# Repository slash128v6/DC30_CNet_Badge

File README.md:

DEF CON 30 CompuNet Badge

Check out the Docs folder...

Here is an informational 'BadUSB'course from the creator of the WiFi Duck: https://learnbadusb.com/ (we are not affiliated and we don't make any money on this)

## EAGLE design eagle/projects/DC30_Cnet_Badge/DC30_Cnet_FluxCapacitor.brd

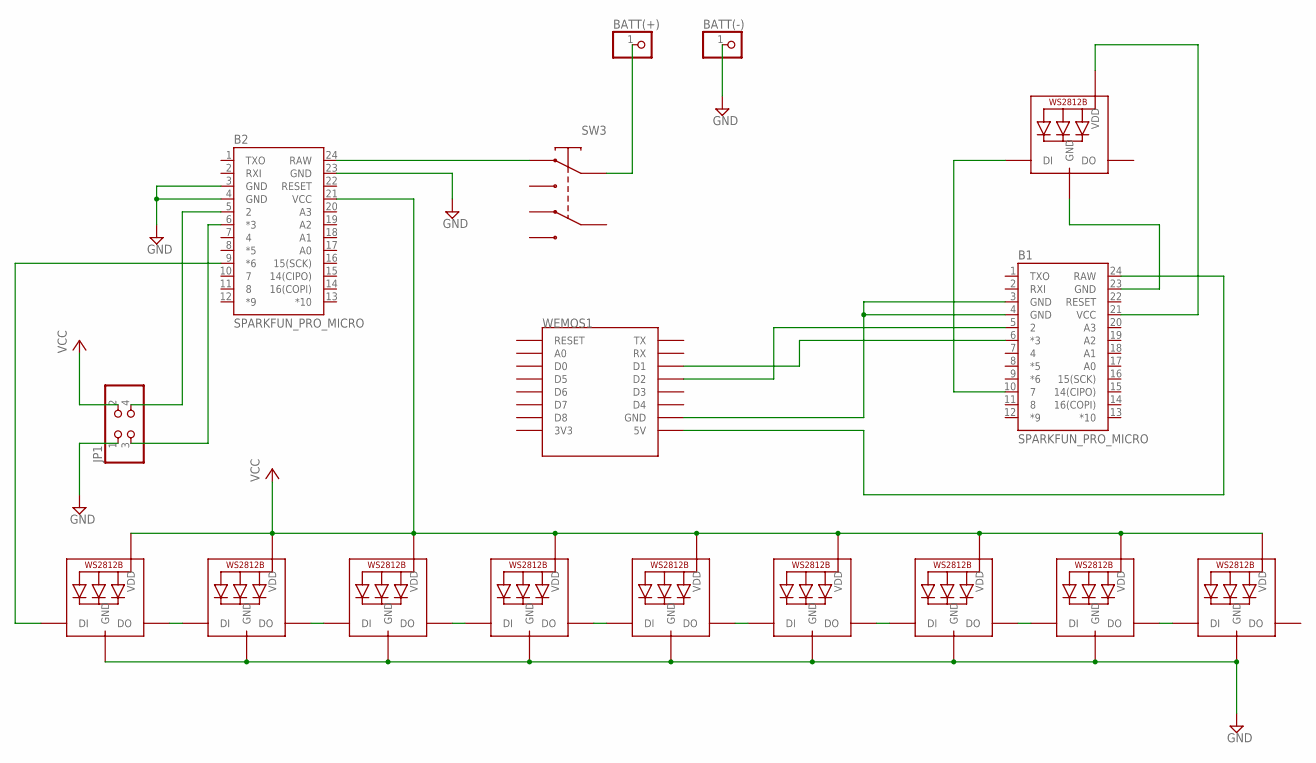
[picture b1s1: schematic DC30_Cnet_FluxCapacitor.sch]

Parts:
B1, B2: SPARKFUN_PRO_MICRO
BATT(+): PINHD-1X1; 1X01
BATT(-): PINHD-1X1; 1X01
JP1: PINHD-2X2; 2X02
LED1, LED2, LED3, LED4, LED5, LED6, LED7, LED8, LED9, LED10: WS2812B5050; WS2812B
SW3: JS202011AQN
WEMOS1: WEMOS-D1-MINI

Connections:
GND: B2.3 (GND), B2.4 (GND), B2.23 (GND), BATT(-).1, JP1.1, LED1.3-GND (GND), LED2.3-GND (GND), LED3.3-GND (GND), LED4.3-GND (GND), LED5.3-GND (GND), LED6.3-GND (GND), LED7.3-GND (GND), LED8.3-GND (GND), LED9.3-GND (GND)
unnamed: B1.10 (7), LED10.4-DIN (DI)
unnamed: BATT(+).1, SW3.P$2 (2)
unnamed: B2.9 (*6), LED1.4-DIN (DI)
unnamed: LED1.2-DOUT (DO), LED2.4-DIN (DI)
unnamed: LED2.2-DOUT (DO), LED3.4-DIN (DI)
unnamed: LED3.2-DOUT (DO), LED4.4-DIN (DI)
unnamed: LED4.2-DOUT (DO), LED5.4-DIN (DI)
unnamed: LED5.2-DOUT (DO), LED6.4-DIN (DI)
unnamed: LED6.2-DOUT (DO), LED7.4-DIN (DI)
unnamed: LED7.2-DOUT (DO), LED8.4-DIN (DI)
unnamed: LED8.2-DOUT (DO), LED9.4-DIN (DI)
unnamed: B2.5 (2), JP1.4
unnamed: B1.3 (GND), B1.4 (GND), WEMOS1.GND
unnamed: B1.24 (RAW), WEMOS1.5V
unnamed: B1.23 (GND), LED10.3-GND (GND)
unnamed: B1.21 (VCC), LED10.1-VDD (VDD)
unnamed: B1.5 (2), WEMOS1.D2
unnamed: B1.6 (*3), WEMOS1.D1
unnamed: B2.6 (*3), JP1.3
unnamed: B2.24 (RAW), SW3.P$1 (1)
VCC: B2.21 (VCC), JP1.2, LED1.1-VDD (VDD), LED2.1-VDD (VDD), LED3.1-VDD (VDD), LED4.1-VDD (VDD), LED5.1-VDD (VDD), LED6.1-VDD (VDD), LED7.1-VDD (VDD), LED8.1-VDD (VDD), LED9.1-VDD (VDD)

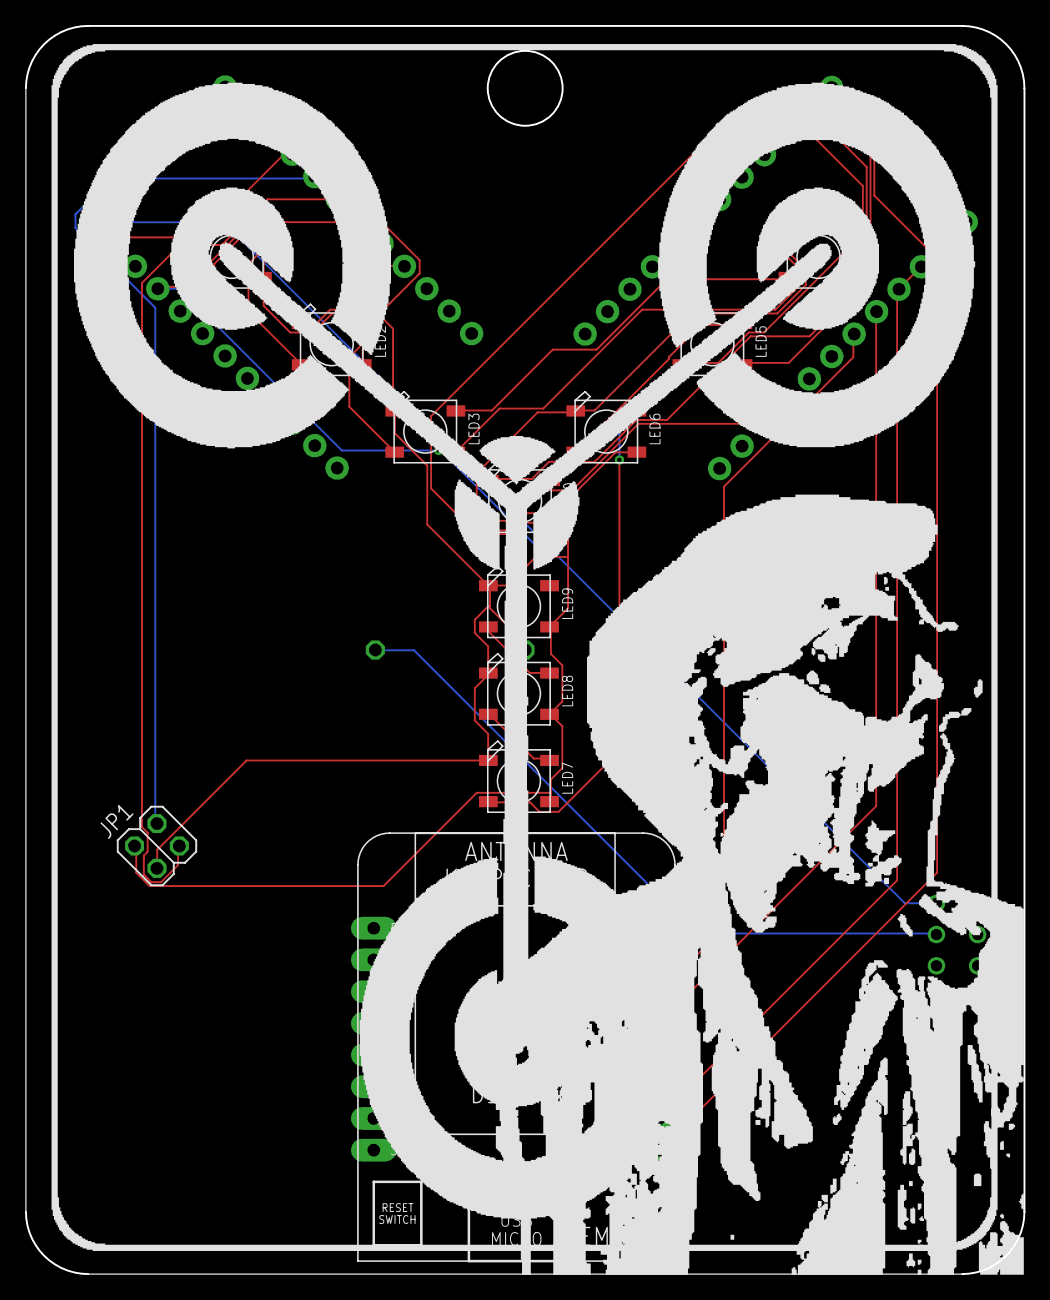
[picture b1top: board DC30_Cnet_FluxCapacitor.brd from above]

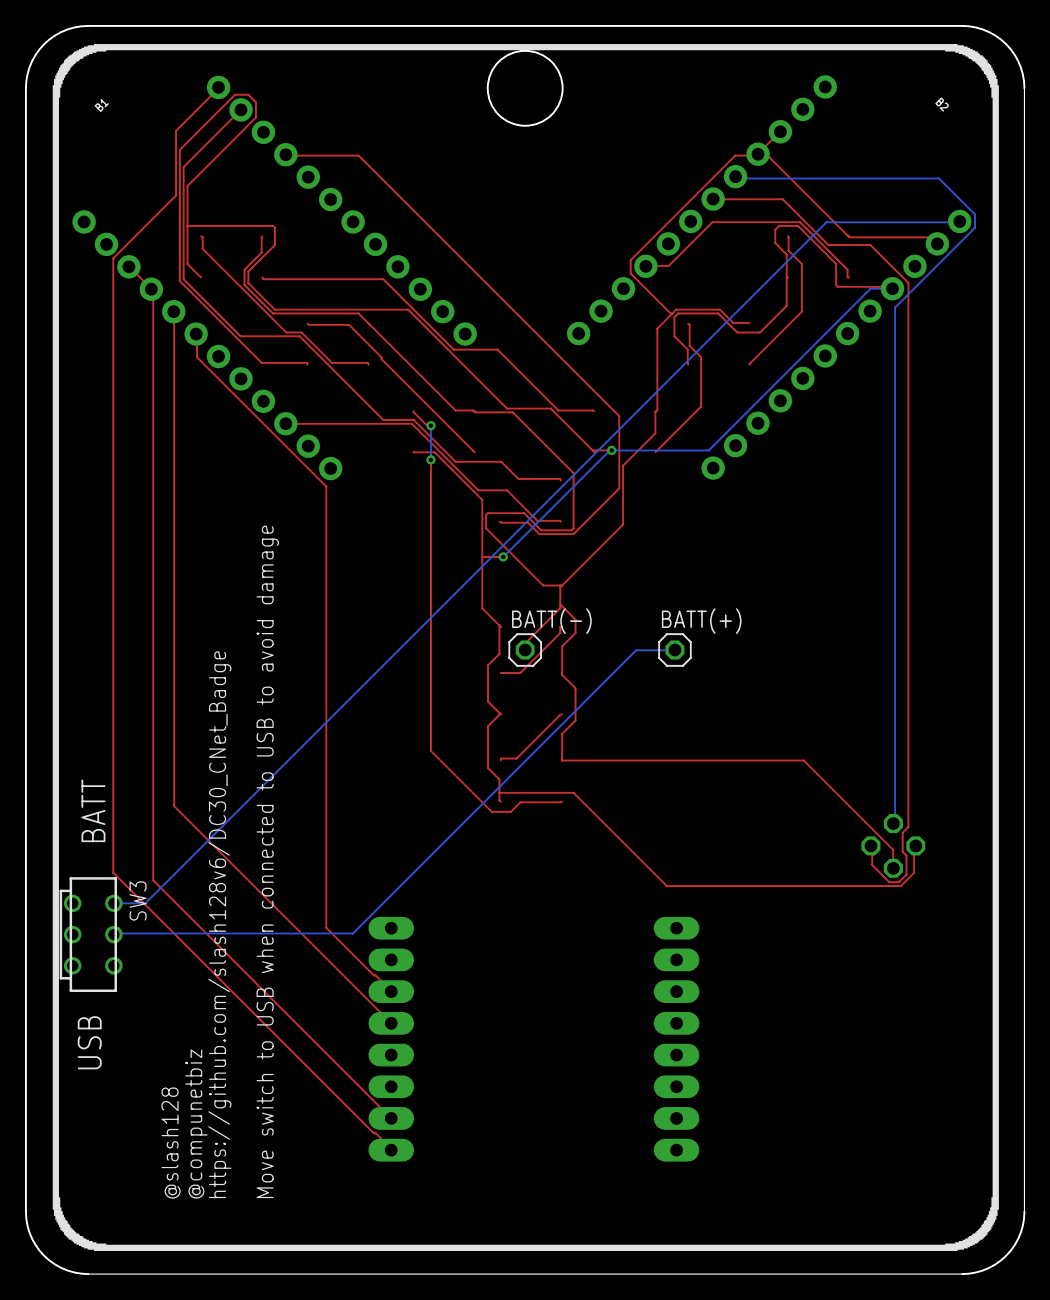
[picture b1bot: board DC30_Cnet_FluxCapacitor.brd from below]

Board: 2 copper layers, 80.0 x 100.0 mm, 17 parts (5 on the bottom side), 22 nets.

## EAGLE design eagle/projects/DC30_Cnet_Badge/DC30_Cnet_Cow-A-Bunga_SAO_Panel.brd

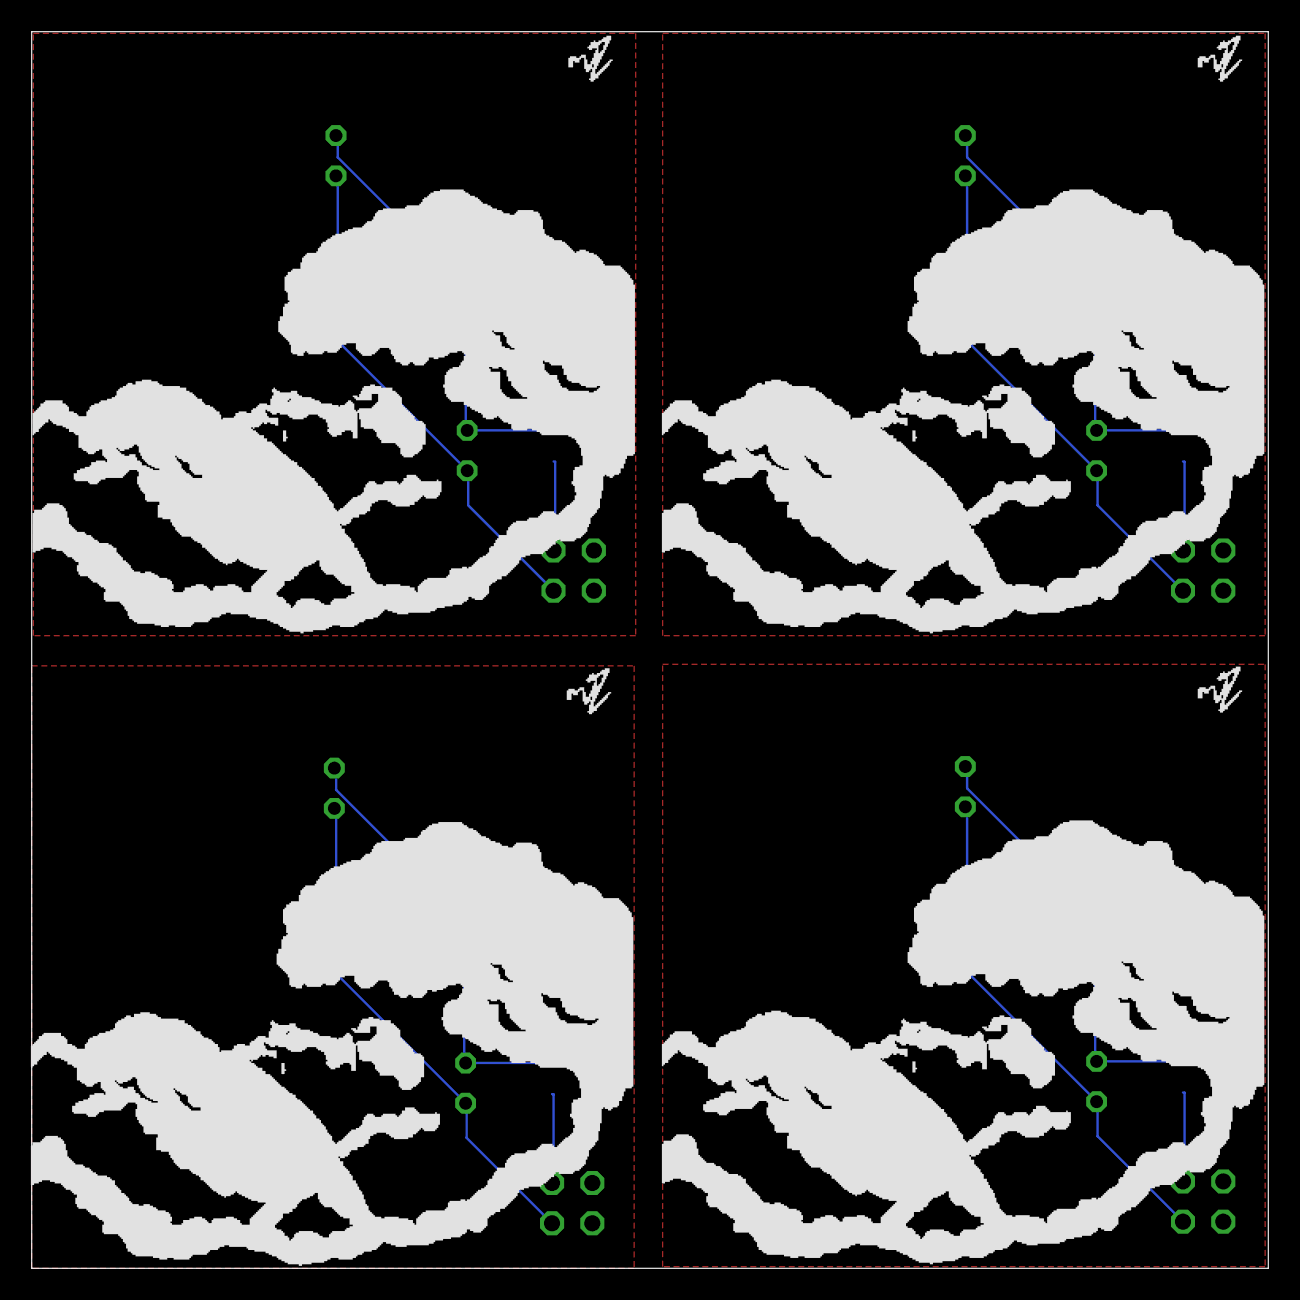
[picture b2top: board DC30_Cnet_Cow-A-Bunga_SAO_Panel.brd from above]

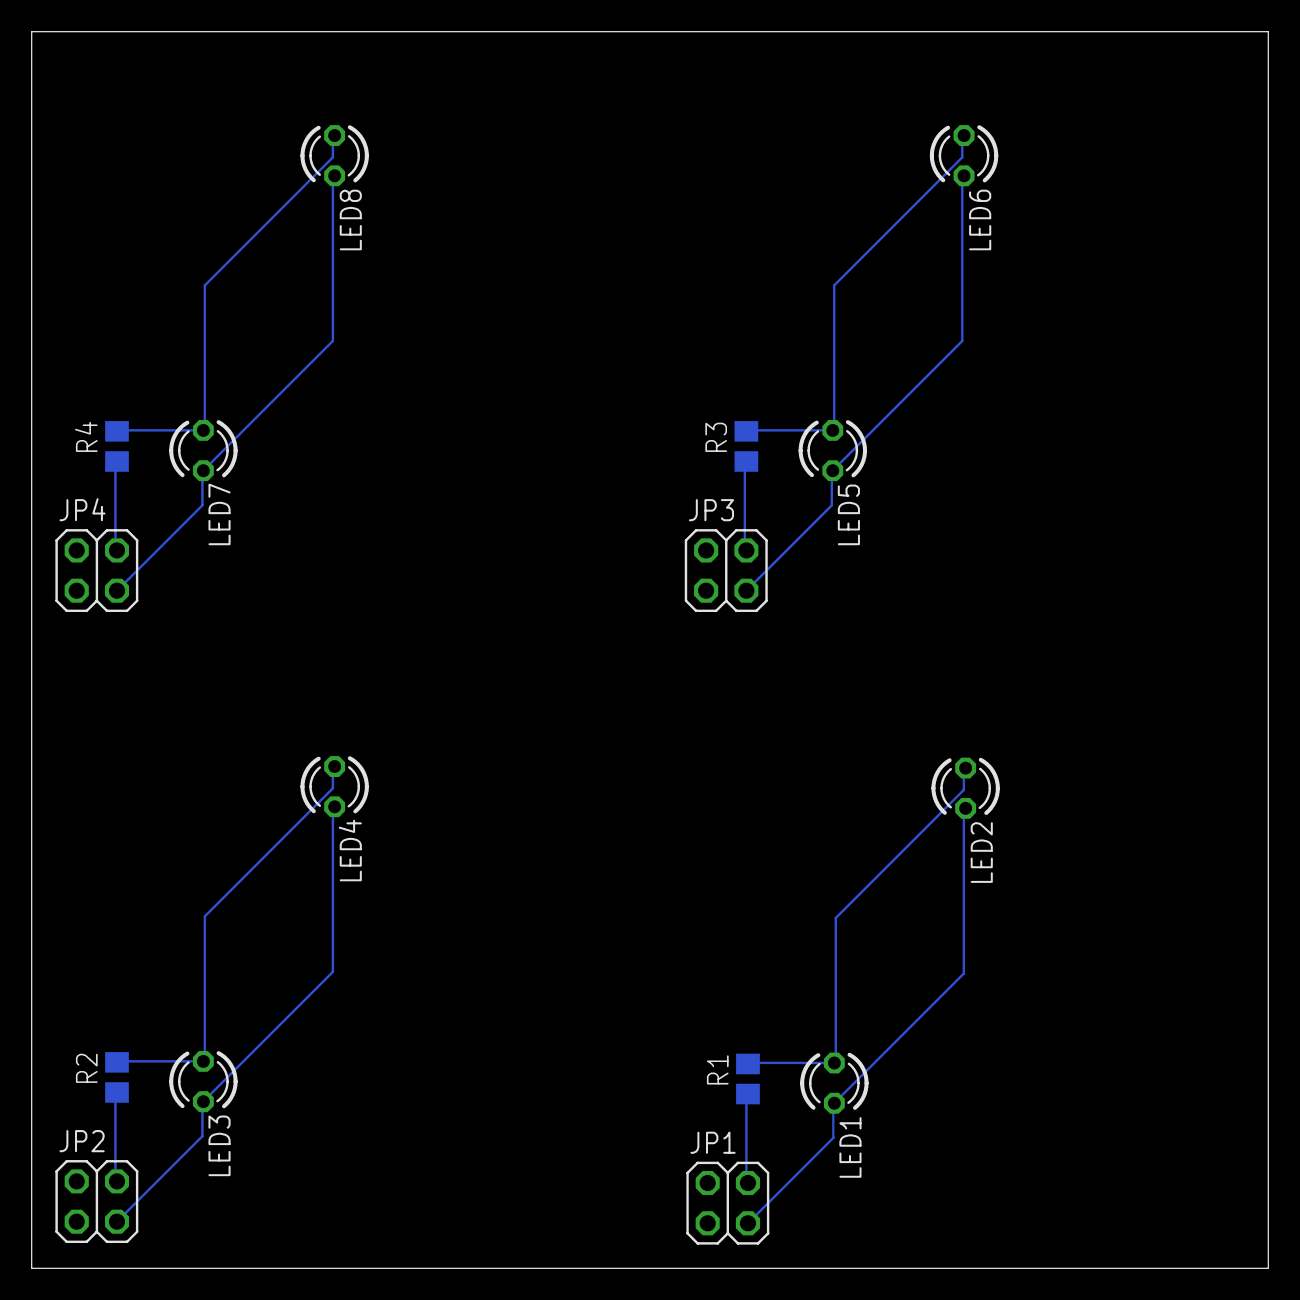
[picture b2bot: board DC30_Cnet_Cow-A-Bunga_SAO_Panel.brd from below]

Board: 2 copper layers, 78.0 x 78.0 mm, 16 parts (16 on the bottom side), 12 nets.

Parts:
JP1, JP2, JP3, JP4: 2X02
LED1, LED2, LED3, LED4, LED5, LED6, LED7, LED8: LED3MM
R1, R2, R3, R4: R0805

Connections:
unnamed: JP1.3, LED1.K, LED2.K
unnamed: JP1.4, R1.1
unnamed: JP2.3, LED3.K, LED4.K
unnamed: LED1.A, LED2.A, R1.2
unnamed: LED3.A, LED4.A, R2.2
unnamed: JP2.4, R2.1
unnamed: JP3.3, LED5.K, LED6.K
unnamed: LED5.A, LED6.A, R3.2
unnamed: JP3.4, R3.1
unnamed: JP4.3, LED7.K, LED8.K
unnamed: LED7.A, LED8.A, R4.2
unnamed: JP4.4, R4.1

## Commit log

2022-04-02 Add files via upload
    Initial Commit
2022-07-26 added Readme.md
2022-07-26 updated docs
2022-07-27 Readme.md updated
2022-08-06 added photos and appendix
2022-08-06 formatting change

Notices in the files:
parts and their libraries:
SparkFun-Boards: Licensing: Creative Commons ShareAlike 4.0 International - https://creativecommons.org/licenses/by-sa/4.0
